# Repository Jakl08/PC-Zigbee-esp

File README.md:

# Hauptdokument: PC Power-Controller (README.md)

## Inhaltsverzeichnis
1. [Projektübersicht und Hardware-Setup](#1-projektübersicht-und-hardware-setup)
2. [Behobene Fehler und Logik-Probleme](#2-behobene-fehler-und-logik-probleme)
3. [Migration auf den Seeed Studio XIAO ESP32C6](#3-migration-auf-den-seeed-studio-xiao-esp32c6)

## See:
* [Hardware und Verkabelung](chapter/hardware-und-verkabelung.md)
* [Software: Python-Skript](chapter/software-python-skript.md)
* [Software: Docker-Umgebung](chapter/software-docker-umgebung.md)
* [Backend: FastAPI Webseite auf Proxmox](chapter/backend-fastapi-webseite-auf-proxmox.md)

<br>

---
---

<br>

## 1. Projektübersicht und Hardware-Setup

Das Projekt ermöglicht die Fernsteuerung und Statusüberwachung eines PCs. Eine webbasierte API (FastAPI) dient als Dashboard, während ein lokaler Controller die physische Schaltung am PC vornimmt und den Status an die Website meldet. 

**Hardware-Verkabelung am Raspberry Pi (3,3V Logik):**
*   **Relais (Low-Level-Trigger):** Verbunden mit GPIO 18. Da es "Low-Level" triggert, muss der Pin beim Start auf `GPIO.HIGH` gesetzt werden, damit das Relais nicht sofort beim Booten anzieht.
*   **PC-Status (Power-LED):** Abgegriffen über einen Spannungsteiler und verbunden mit GPIO 17 (Pull-Down). Ein anliegendes `HIGH`-Signal bedeutet, der PC ist eingeschaltet.

### System-Architektur

```drawio
<mxGraphModel dx="1000" dy="1000" grid="1" gridSize="10" guides="1" tooltips="1" connect="1" arrows="1" fold="1" page="1" pageScale="1" pageWidth="827" pageHeight="1169" math="0" shadow="0" background="#ffffff">
  <root>
    <mxCell id="0" />
    <mxCell id="1" parent="0" />
    <mxCell id="2" value="FastAPI Web-Dashboard&#xa;(Domain aus .env)" style="rounded=1;whiteSpace=wrap;html=1;fillColor=#dae8fc;strokeColor=#6c8ebf;fontStyle=1" vertex="1" parent="1">
      <mxGeometry x="120" y="120" width="200" height="80" as="geometry" />
    </mxCell>
    <mxCell id="3" value="Hardware-Controller&#xa;(Raspberry Pi / ESP32C6)" style="rounded=1;whiteSpace=wrap;html=1;fillColor=#d5e8d4;strokeColor=#82b366;fontStyle=1" vertex="1" parent="1">
      <mxGeometry x="480" y="120" width="200" height="80" as="geometry" />
    </mxCell>
    <mxCell id="4" value="PC-Hardware&#xa;&lt;br&gt;- Power-Button (Relais)&lt;br&gt;- Power-LED (Status-Pin)" style="rounded=1;whiteSpace=wrap;html=1;fillColor=#ffe6cc;strokeColor=#d79b00;" vertex="1" parent="1">
      <mxGeometry x="480" y="280" width="200" height="80" as="geometry" />
    </mxCell>
    <mxCell id="5" value="API Polling (30s) &amp;amp; Sync" style="edgeStyle=orthogonalEdgeStyle;rounded=0;orthogonalLoop=1;jettySize=auto;html=1;startArrow=classic;startFill=1;strokeWidth=2;" edge="1" parent="1" source="2" target="3">
      <mxGeometry relative="1" as="geometry" />
    </mxCell>
    <mxCell id="6" value="Relais schalten (LOW-Trigger)" style="edgeStyle=orthogonalEdgeStyle;rounded=0;orthogonalLoop=1;jettySize=auto;html=1;" edge="1" parent="1" source="3" target="4">
      <mxGeometry x="-0.5" relative="1" as="geometry">
        <Array as="points"><mxPoint x="530" y="240" /><mxPoint x="530" y="240" /></Array>
      </mxGeometry>
    </mxCell>
    <mxCell id="7" value="Status prüfen (3,3V)" style="edgeStyle=orthogonalEdgeStyle;rounded=0;orthogonalLoop=1;jettySize=auto;html=1;dashed=1;startArrow=classic;startFill=1;endArrow=none;endFill=0;" edge="1" parent="1" source="3" target="4">
      <mxGeometry relative="1" as="geometry">
        <Array as="points"><mxPoint x="630" y="240" /><mxPoint x="630" y="240" /></Array>
      </mxGeometry>
    </mxCell>
  </root>
</mxGraphModel>
```

<br><br>

## 2. Behobene Fehler und Logik-Probleme

Während der Entwicklung traten verschiedene logische Hürden auf, die wie folgt gelöst wurden:

### Fehler 1: Der `SyntaxError` bei globalen Variablen
*   **Problem:** Das Deklarieren von `global last_pc_status_phy` innerhalb der `try/while`-Schleifenstruktur führte zu `SyntaxError: name is assigned to before global declaration`, weil die Variable weiter oben im Block bereits verarbeitet wurde.
*   **Lösung:** Verzicht auf das `global`-Schlüsselwort. Stattdessen wird der bekannte Status als Argument an die Funktion übergeben: `def check_hardware_integrity(expected_state):`. Die Schleife ruft die Funktion dann gezielt mit `check_hardware_integrity(last_pc_status_phy)` auf.

### Fehler 2: Relais klickt mehrfach / Fehlalarme
*   **Problem:** Wenn die API ein Anschalten forderte, triggerte das Skript das Relais, setzte die Status-Variable auf "AN" und prüfte kurz danach erneut. Da der PC aber 10-15 Sekunden braucht, bis die Power-LED leuchtet, warf das Skript einen Fehlalarm ("Pin ist LOW, Variable ist True"), setzte alles auf "AUS" zurück und triggerte das Relais im nächsten Durchlauf erneut.
*   **Lösung:** Nach dem Auslösen des Relais wurde eine Verzögerungs-Schleife (bis zu 15 Sekunden) eingebaut, in der das Skript aktiv wartet, bis sich der tatsächliche GPIO-Pin-Status ändert (`if get_pc_status_phy(): break`), bevor der neue Zustand in der Variablen gespeichert wird.

### Fehler 3: Status-Sync auf der Website schlägt fehl
*   **Problem:** Die API forderte nicht das Feld `is_on` für Schaltwünsche, sondern `is_requested`. Zudem gab es im Exception-Block einen Namensfehler (`pc_status_phy` statt dem Funktionsaufruf `get_pc_status_phy()`), wodurch der POST-Request fehlschlug.
*   **Lösung:** Das Skript fragt nun `status_dict.get("is_requested", False)` ab. Im Exception-Block wird der Status frisch ausgelesen, in die Schleifenvariable geschrieben und fehlerfrei an `report_status_to_api(last_pc_status_phy)` übergeben.

<br><br>

## 3. Migration auf den Seeed Studio XIAO ESP32C6

Der Raspberry Pi soll durch den weitaus kompakteren und stromsparenderen **Seeed Studio XIAO ESP32C6** ersetzt werden. 

*   **Hardware-Kompatibilität:** Da der ESP32C6 ebenfalls mit einer **3,3V-Logik** arbeitet, können die drei Pins des Relais (VCC, GND, Signal) und die zwei Pins des Status-Sensors (GND, Signal vom Spannungsteiler) 1:1 vom Raspberry Pi übernommen werden.
*   **Software-Anpassung:** Das bestehende Python-Skript (`RPi.GPIO`) läuft auf dem ESP32 nicht direkt. Es müsste auf MicroPython (`machine.Pin`) umgeschrieben werden.
*   **Die Zigbee-Einschränkung:** Obwohl der ESP32C6 einen Zigbee-Chip besitzt, ist es in MicroPython aktuell nicht ohne extremen Programmieraufwand (C/C++ über ESP-IDF) möglich, den Mikrocontroller als standardisiertes Zigbee-Endgerät in einem bestehenden Zigbee2MQTT-Netzwerk anzulernen.
*   **Der empfohlene Weg (WLAN & ESPHome):** Da der zentrale Pi im Netzwerk ohnehin Home Assistant und Mosquitto bereitstellt, wird empfohlen, den ESP32C6 über WLAN mit **ESPHome** zu flashen. Über eine simple YAML-Konfiguration lassen sich das Relais (Switch) und der Status (Sensor) definieren. Der Controller taucht dann automatisch über das Netzwerk in Home Assistant auf und macht jegliche Python- und Zigbee-Umwege überflüssig. Alternativ kann MicroPython in Kombination mit einer MQTT-Bibliothek über WLAN genutzt werden.

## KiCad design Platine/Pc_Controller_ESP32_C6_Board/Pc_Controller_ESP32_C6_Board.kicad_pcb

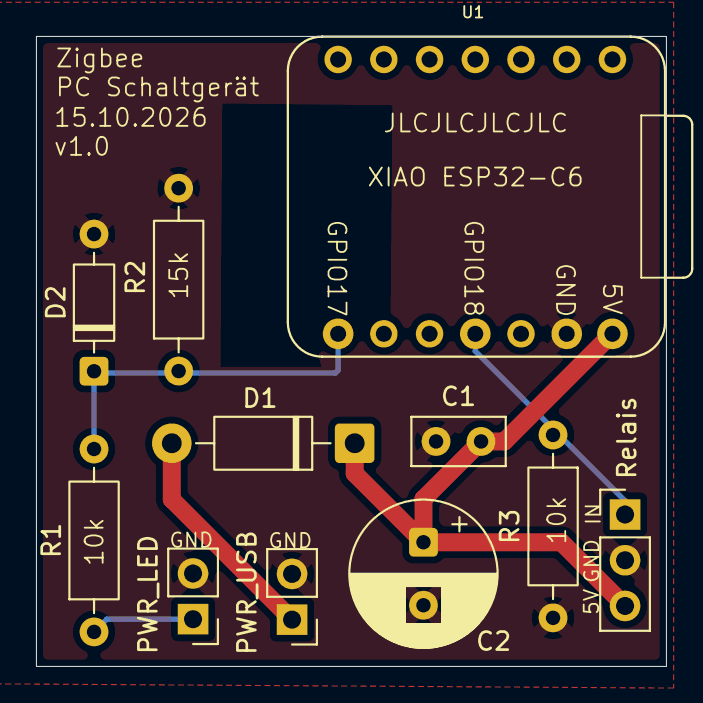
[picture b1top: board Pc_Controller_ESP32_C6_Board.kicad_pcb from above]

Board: 2 copper layers, 35.0 x 35.0 mm, 11 parts (0 on the bottom side), 6 nets.

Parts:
C1: 100 nF; C_Disc_D5.0mm_W2.5mm_P2.50mm
C2: 220 uF; CP_Radial_D8.0mm_P3.50mm
D1: D_Schottky; D_DO-41_SOD81_P10.16mm_Horizontal
D2: D_Zener; D_DO-35_SOD27_P7.62mm_Horizontal
PWR_LED: Mainboard PWR_LED; PinHeader_1x02_P2.54mm_Vertical
PWR_USB: Mainboard_USB_PWR; PinHeader_1x02_P2.54mm_Vertical
R1, R3: 10k; R_Axial_DIN0207_L6.3mm_D2.5mm_P10.16mm_Horizontal
R2: 15k; R_Axial_DIN0207_L6.3mm_D2.5mm_P10.16mm_Horizontal
Relais: Relais 5V High Trigger; PinHeader_1x03_P2.54mm_Vertical
U1: XIAO ESP32-C6; XIAO-ESP32-C6-DIP

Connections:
GND: C1.1, C2.2, D2.2 (A), PWR_LED.2 (PWR_LED-), PWR_USB.2 (PWR-), R2.2, R3.2, Relais.2 (DC-), U1.13 (GND)
unnamed: D1.2 (A), PWR_USB.1 (PWR+)
unnamed: C1.2, C2.1, D1.1 (K), Relais.3 (DC+), U1.14 (VBUS)
unnamed: D2.1 (K), R1.2, R2.1, U1.8 (D7)
unnamed: R3.1, Relais.1 (IN1), U1.11 (D10)
unnamed: PWR_LED.1 (PWR_LED+), R1.1
